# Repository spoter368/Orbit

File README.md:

# Orbit keyboard
A split ergonomic keyboard for all

#### In light of recent claims that I am 100% liable for any of my open source PCBs, I am adding this disclaimer.
#### I provide these PCBs as a reference for designing keyboard PCBs. Using them within your projects will require a will to do research of one's own and to learn the workings of them, potentially fixing issues if they exist.
# I provide these PCBs without liability and without any guarantees regarding functionality, as expressed in the licenses under which these PCBs are licensed.

## Features
- Ergonomic layout based on the [crkbd](https://github.com/foostan/crkbd)
- All on-board components; no separate controller board
- USB Type-C and in-switch backlight
- Alps SKCL/M and MX compatibility
- Built-in overcurrent, reverse voltage, and ESD protection.
- Pre-panelized in a single PCB file for easy production
- Keyboard-Layout-Editor data is available [here](http://www.keyboard-layout-editor.com/#/gists/53ebf59524de12515cb7e2e6de94f0d6).

## Designed for all
- This keyboard remains close to typical QWERTY layout in key positioning.
- Most keys remain in their typical locations, which allows easy migration from standard layout keyboards.
- Whether new to ergonomic layouts or already an avid adopter, Orbit will suit your needs.

## Electrical side
- The incoming power is handled as shown:

- VCC/Raw is the raw power fed through the USB connector. The ESD protection IC is bound to here.
- VBUS is "stable raw power" after being passed through a polyfuse. Used for upstream detection, for a downstream Schottky diode prevents flow from 5V into VBUS. In other words, VBUS is only at 5V when fed from upstream USB.
- 5V is the "stable power" after passing through a Schottky diode. Used for powering MCU, LEDs, and other split half. Power from the other half feeds here, for it has already been filtered on the other side.
- Measures are taken to isolate the LED, MCU, and split connection 5V as upstream as possible to prevent interference.

## Aesthetics
- Ground plane is limited to critical parts for aesthetic reasons.
- Top side of PCB is mostly covered with soldermask.

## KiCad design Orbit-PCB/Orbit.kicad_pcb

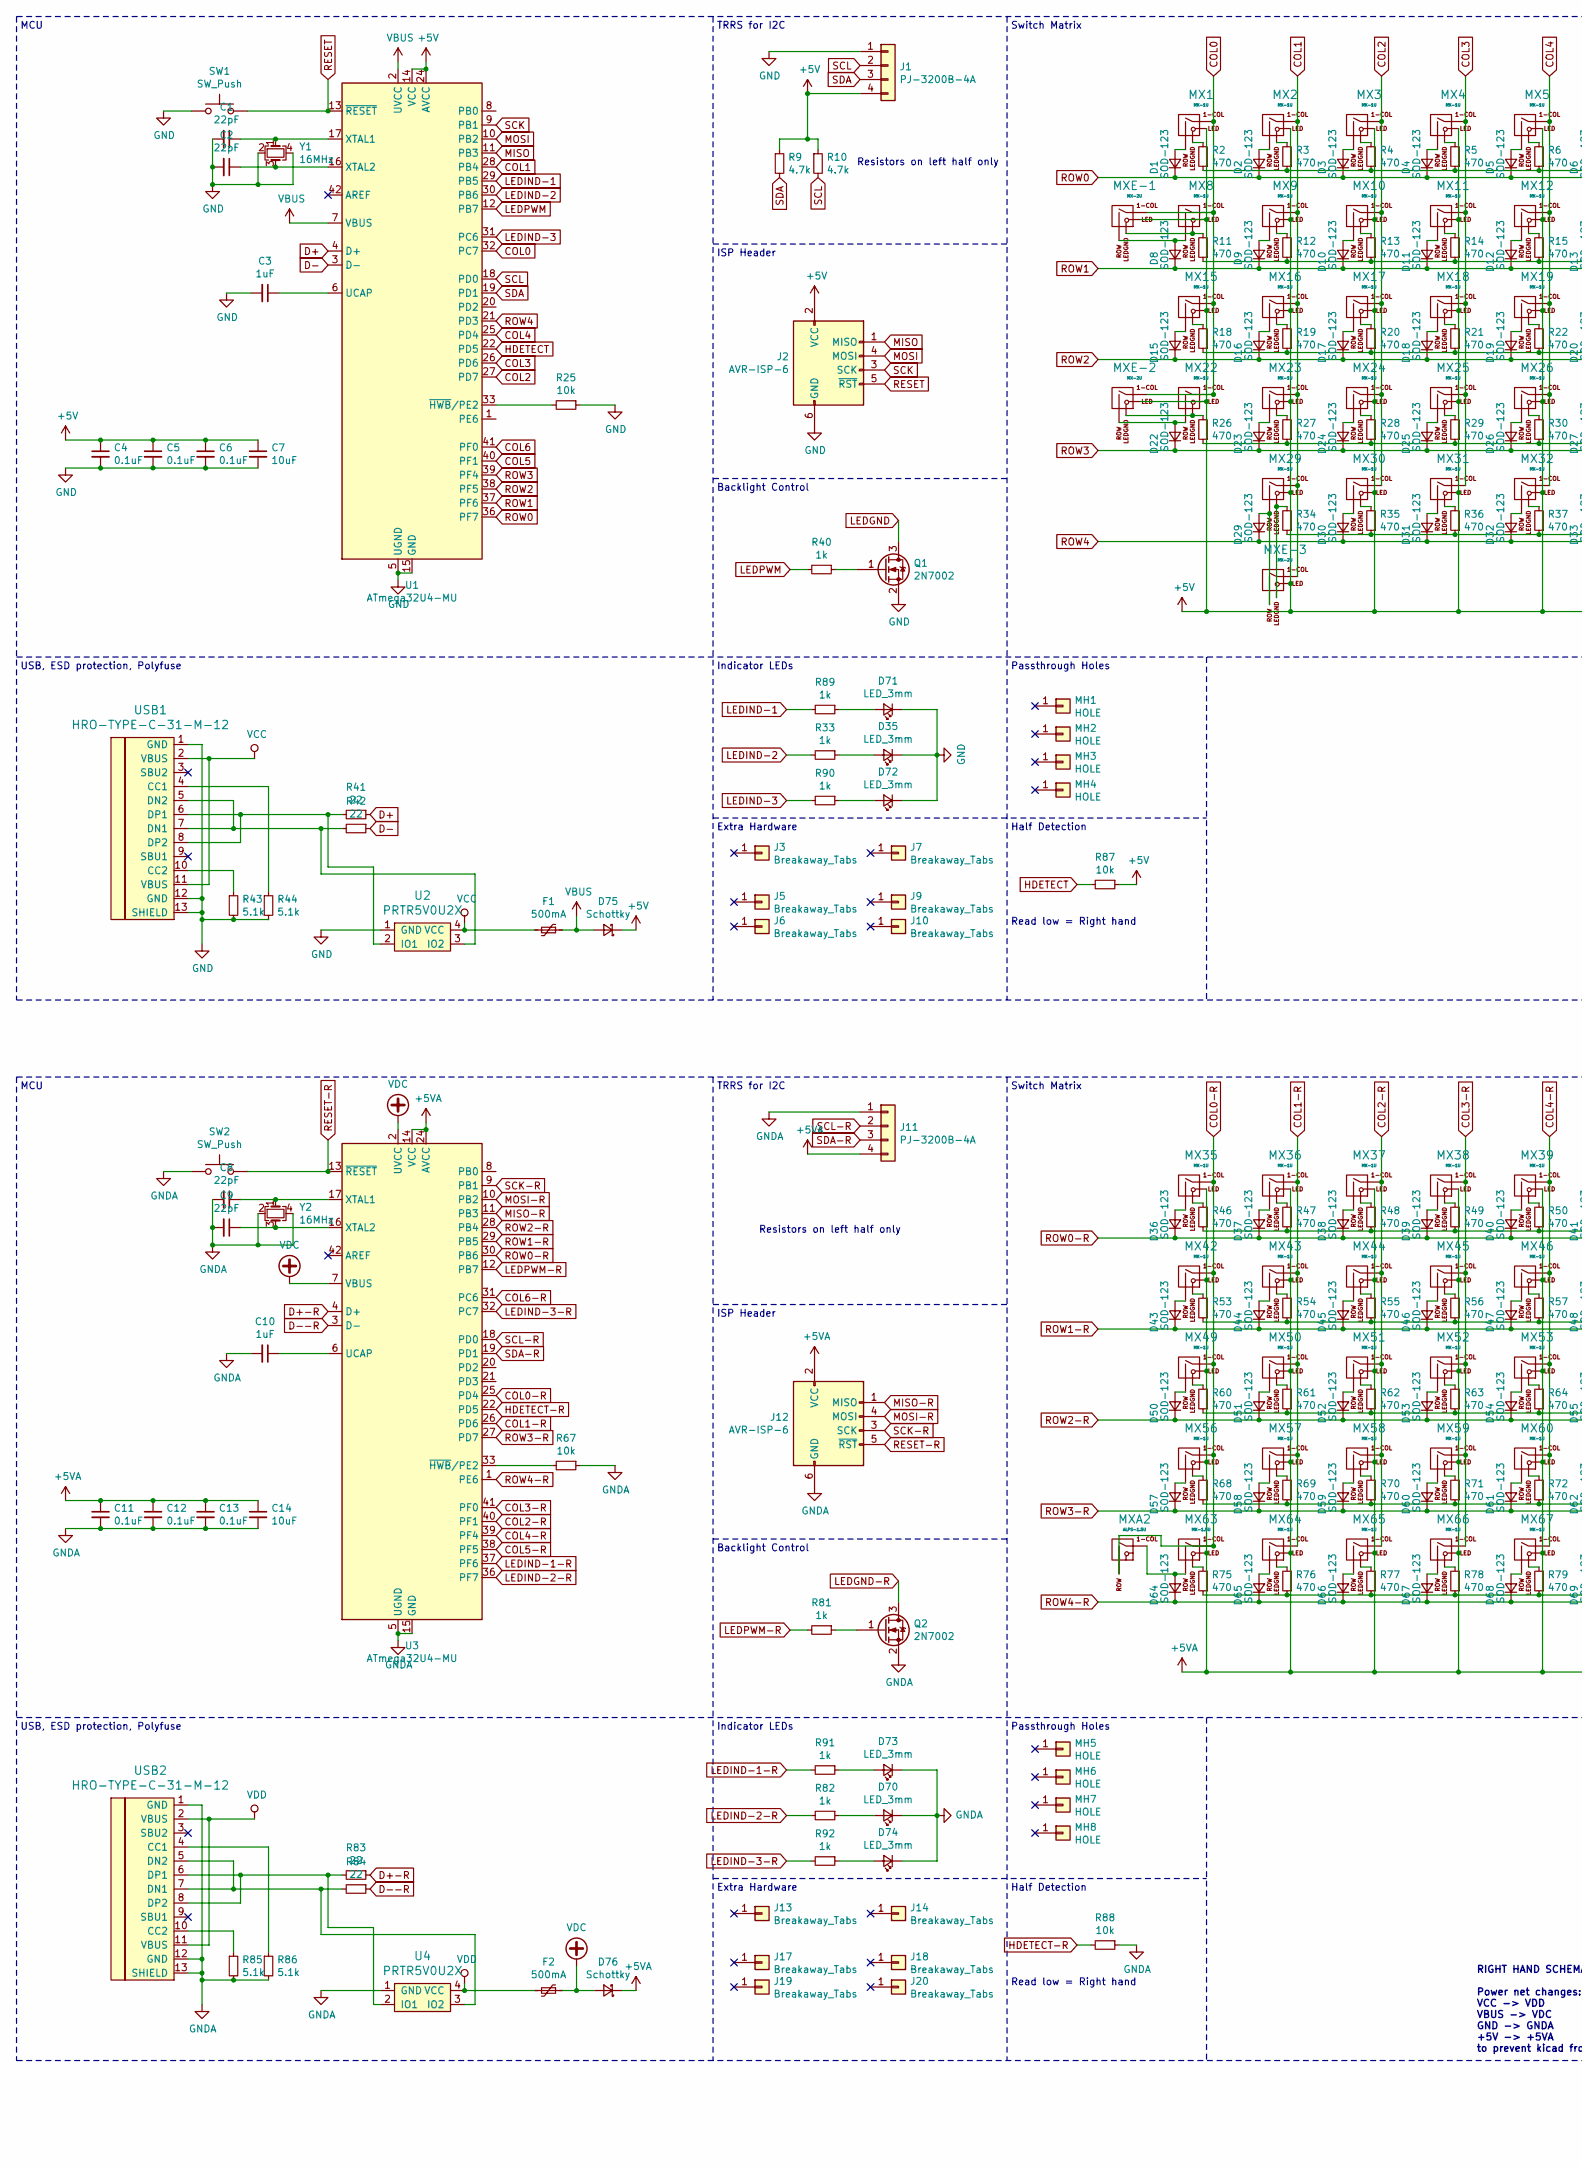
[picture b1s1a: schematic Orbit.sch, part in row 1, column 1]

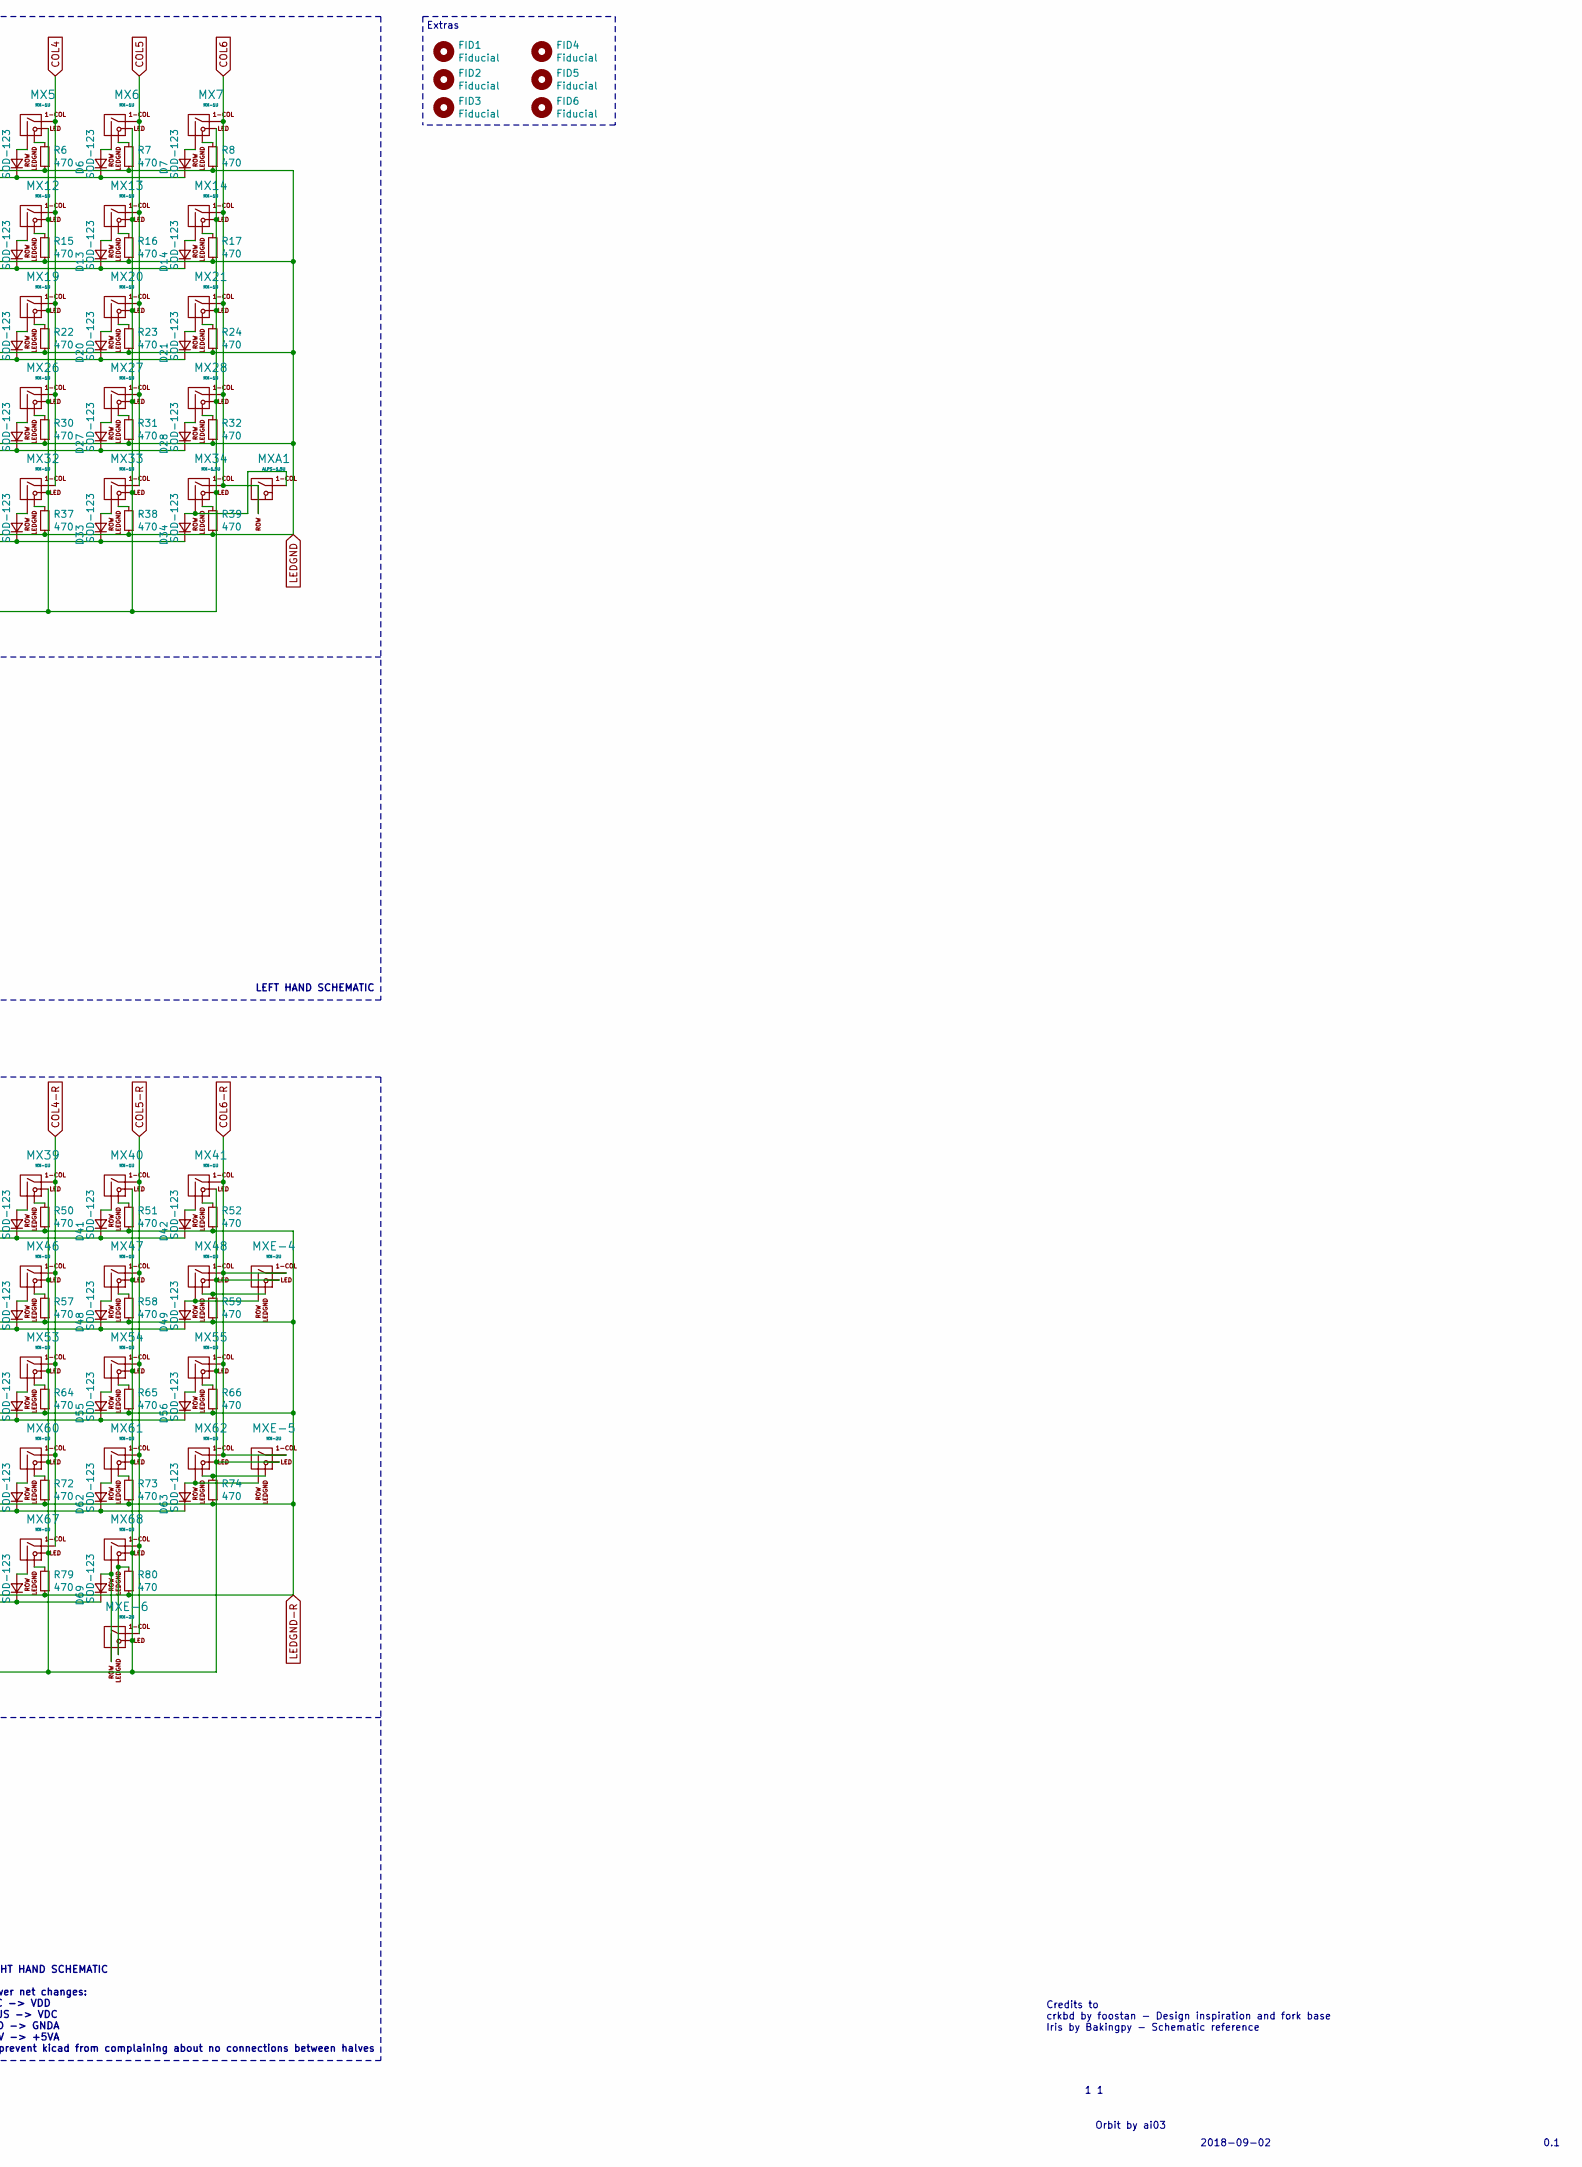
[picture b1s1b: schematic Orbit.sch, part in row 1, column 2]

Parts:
C1, C2, C8, C9: 22pF; C_0603_1608Metric
C3, C10: 1uF; C_0603_1608Metric
C4, C5, C6, C11, C12, C13: 0.1uF; C_0603_1608Metric
C7, C14: 10uF; C_0603_1608Metric
D1, D2, D3, D4, D5, D6, D7, D8, D9, D10, D11, D12, D13, D14, D15, D16, D17, D18, D19, D20, D21, D22, D23, D24, D25, D26, D27, D28, D29, D30, D31, D32, D33, D34, D36, D37, D38, D39, D40, D41, D42, D43, D44, D45, D46, D47, D48, D49, D50, D51, D52, D53, D54, D55, D56, D57, D58, D59, D60, D61, D62, D63, D64, D65, D66, D67, D68, D69: SOD-123; D_SOD-123
D35, D70, D71, D72, D73, D74: LED_3mm; LED_D3.0mm
D75, D76: Schottky; D_SOD-123
F1, F2: 500mA; Fuse_SMD1206_Reflow
FID1, FID2, FID3, FID4, FID5, FID6: Fiducial; Fiducial_1mm_Dia_2.54mm_Outer_CopperTop
J1, J11: PJ-3200B-4A
J2, J12: AVR-ISP-6; Reset_Pretty
J3, J5, J6, J7, J9, J10, J13, J14, J17, J18, J19, J20: Breakaway_Tabs; breakaway-mousebites
MH1, MH2, MH3, MH4, MH5, MH6, MH7, MH8: HOLE; MountingHole_3.2mm_M3_ISO7380
MX1, MX2, MX3, MX4, MX5, MX6, MX7, MX8, MX9, MX10, MX11, MX12, MX13, MX14, MX15, MX16, MX17, MX18, MX19, MX20, MX21, MX22, MX23, MX24, MX25, MX26, MX27, MX28, MX29, MX30, MX31, MX32, MX33, MX35, MX36, MX37, MX38, MX39, MX40, MX41, MX42, MX43, MX44, MX45, MX46, MX47, MX48, MX49, MX50, MX51, MX52, MX53, MX54, MX55, MX56, MX57, MX58, MX59, MX60, MX61, MX62, MX64, MX65, MX66, MX67, MX68: MX-1U
MX34, MX63: MX-1.5U; MXOnly-1.5U-Vertical
MXA1, MXA2: ALPS-1.5U
MXE-1, MXE-2: MX-2U
MXE-3, MXE-4, MXE-5, MXE-6: MX-2U; MX-2U-ReversedStabilizers
Q1, Q2: 2N7002; SOT-23
R2, R3, R4, R5, R6, R7, R8, R11, R12, R13, R14, R15, R16, R17, R18, R19, R20, R21, R22, R23, R24, R26, R27, R28, R29, R30, R31, R32, R34, R35, R36, R37, R38, R39, R46, R47, R48, R49, R50, R51, R52, R53, R54, R55, R56, R57, R58, R59, R60, R61, R62, R63, R64, R65, R66, R68, R69, R70, R71, R72, R73, R74, R75, R76, R77, R78, R79, R80: 470; R_0805_2012Metric
R9, R10: 4.7k; R_0805_2012Metric
R25, R67, R87, R88: 10k; R_0805_2012Metric
R33, R40, R81, R82, R89, R90, R91, R92: 1k; R_0805_2012Metric
R41, R42, R83, R84: 22; R_0805_2012Metric
R43, R44, R85, R86: 5.1k; R_0805_2012Metric
SW1, SW2: SW_Push; SKQGADE010
U1, U3: ATmega32U4-MU; QFN-44-1EP_7x7mm_Pitch0.5mm
U2, U4: PRTR5V0U2X; SOT143B
USB1, USB2: HRO-TYPE-C-31-M-12; HRO-TYPE-C-31-M-12-Assembly
Y1, Y2: 16MHz; Crystal_SMD_3225-4pin_3.2x2.5mm

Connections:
+5V: C4.1, C5.1, C6.1, C7.1, D75.1 (K), J1.4, J2.2 (VCC), MX1.3 (LED), MX2.3 (LED), MX3.3 (LED), MX4.3 (LED), MX5.3 (LED), MX6.3 (LED), MX7.3 (LED), MX8.3 (LED), MX9.3 (LED), MX10.3 (LED), MX11.3 (LED), MX12.3 (LED), MX13.3 (LED), MX14.3 (LED), MX15.3 (LED), MX16.3 (LED), MX17.3 (LED), MX18.3 (LED), MX19.3 (LED), MX20.3 (LED), MX21.3 (LED), MX22.3 (LED), MX23.3 (LED), MX24.3 (LED), MX25.3 (LED), MX26.3 (LED), MX27.3 (LED), MX28.3 (LED), MX29.3 (LED), MX30.3 (LED), MX31.3 (LED), MX32.3 (LED), MX33.3 (LED), MX34.3 (LED), MXE-1.3 (LED), MXE-2.3 (LED), MXE-3.3 (LED), R9.1, R10.1, R87.1, U1.14 (VCC), U1.24 (AVCC), U1.34 (VCC), U1.44 (AVCC)
+5VA: C11.1, C12.1, C13.1, C14.1, D76.1 (K), J11.4, J12.2 (VCC), MX35.3 (LED), MX36.3 (LED), MX37.3 (LED), MX38.3 (LED), MX39.3 (LED), MX40.3 (LED), MX41.3 (LED), MX42.3 (LED), MX43.3 (LED), MX44.3 (LED), MX45.3 (LED), MX46.3 (LED), MX47.3 (LED), MX48.3 (LED), MX49.3 (LED), MX50.3 (LED), MX51.3 (LED), MX52.3 (LED), MX53.3 (LED), MX54.3 (LED), MX55.3 (LED), MX56.3 (LED), MX57.3 (LED), MX58.3 (LED), MX59.3 (LED), MX60.3 (LED), MX61.3 (LED), MX62.3 (LED), MX63.3 (LED), MX64.3 (LED), MX65.3 (LED), MX66.3 (LED), MX67.3 (LED), MX68.3 (LED), MXE-4.3 (LED), MXE-5.3 (LED), MXE-6.3 (LED), U3.14 (VCC), U3.24 (AVCC), U3.34 (VCC), U3.44 (AVCC)
COL0: MX1.1 (COL), MX8.1 (COL), MX15.1 (COL), MX22.1 (COL), MXE-1.1 (COL), MXE-2.1 (COL), U1.32 (PC7)
COL0-R: MX35.1 (COL), MX42.1 (COL), MX49.1 (COL), MX56.1 (COL), MX63.1 (COL), MXA2.2 (ROW), U3.25 (PD4)
COL1: MX2.1 (COL), MX9.1 (COL), MX16.1 (COL), MX23.1 (COL), MX29.1 (COL), MXE-3.1 (COL), U1.28 (PB4)
COL1-R: MX36.1 (COL), MX43.1 (COL), MX50.1 (COL), MX57.1 (COL), MX64.1 (COL), U3.26 (PD6)
COL2: MX3.1 (COL), MX10.1 (COL), MX17.1 (COL), MX24.1 (COL), MX30.1 (COL), U1.27 (PD7)
COL2-R: MX37.1 (COL), MX44.1 (COL), MX51.1 (COL), MX58.1 (COL), MX65.1 (COL), U3.40 (PF1)
COL3: MX4.1 (COL), MX11.1 (COL), MX18.1 (COL), MX25.1 (COL), MX31.1 (COL), U1.26 (PD6)
COL3-R: MX38.1 (COL), MX45.1 (COL), MX52.1 (COL), MX59.1 (COL), MX66.1 (COL), U3.41 (PF0)
COL4: MX5.1 (COL), MX12.1 (COL), MX19.1 (COL), MX26.1 (COL), MX32.1 (COL), U1.25 (PD4)
COL4-R: MX39.1 (COL), MX46.1 (COL), MX53.1 (COL), MX60.1 (COL), MX67.1 (COL), U3.39 (PF4)
COL5: MX6.1 (COL), MX13.1 (COL), MX20.1 (COL), MX27.1 (COL), MX33.1 (COL), U1.40 (PF1)
COL5-R: MX40.1 (COL), MX47.1 (COL), MX54.1 (COL), MX61.1 (COL), MX68.1 (COL), MXE-6.1 (COL), U3.38 (PF5)
COL6: MX7.1 (COL), MX14.1 (COL), MX21.1 (COL), MX28.1 (COL), MX34.1 (COL), MXA1.2 (ROW), U1.41 (PF0)
COL6-R: MX41.1 (COL), MX48.1 (COL), MX55.1 (COL), MX62.1 (COL), MXE-4.1 (COL), MXE-5.1 (COL), U3.31 (PC6)
D+: R41.1, U1.4 (D+)
D+-R: R83.1, U3.4 (D+)
D-: R42.1, U1.3 (D-)
D--R: R84.1, U3.3 (D-)
GND: C1.2, C2.2, C3.2, C4.2, C5.2, C6.2, C7.2, D35.1 (K), D71.1 (K), D72.1 (K), J1.1, J2.6 (GND), Q1.2 (S), R25.1, R43.2, R44.2, SW1.1, U1.5 (UGND), U1.15 (GND), U1.23 (GND), U1.35 (GND), U1.43 (GND), U1.45 (GND), U2.1 (GND), USB1.1 (GND), USB1.12 (GND), USB1.13 (SHIELD), Y1.2, Y1.4
GNDA: C8.2, C9.2, C10.2, C11.2, C12.2, C13.2, C14.2, D70.1 (K), D73.1 (K), D74.1 (K), J11.1, J12.6 (GND), Q2.2 (S), R67.1, R85.2, R86.2, R88.1, SW2.1, U3.5 (UGND), U3.15 (GND), U3.23 (GND), U3.35 (GND), U3.43 (GND), U3.45 (GND), U4.1 (GND), USB2.1 (GND), USB2.12 (GND), USB2.13 (SHIELD), Y2.2, Y2.4
HDETECT: R87.2, U1.22 (PD5)
HDETECT-R: R88.2, U3.22 (PD5)
LEDGND: Q1.3 (D), R2.1, R3.1, R4.1, R5.1, R6.1, R7.1, R8.1, R11.1, R12.1, R13.1, R14.1, R15.1, R16.1, R17.1, R18.1, R19.1, R20.1, R21.1, R22.1, R23.1, R24.1, R26.1, R27.1, R28.1, R29.1, R30.1, R31.1, R32.1, R34.1, R35.1, R36.1, R37.1, R38.1, R39.1
LEDGND-R: Q2.3 (D), R46.1, R47.1, R48.1, R49.1, R50.1, R51.1, R52.1, R53.1, R54.1, R55.1, R56.1, R57.1, R58.1, R59.1, R60.1, R61.1, R62.1, R63.1, R64.1, R65.1, R66.1, R68.1, R69.1, R70.1, R71.1, R72.1, R73.1, R74.1, R75.1, R76.1, R77.1, R78.1, R79.1, R80.1
LEDIND-1: R89.2, U1.29 (PB5)
LEDIND-1-R: R91.2, U3.37 (PF6)
LEDIND-2: R33.2, U1.30 (PB6)
LEDIND-2-R: R82.2, U3.36 (PF7)
LEDIND-3: R90.2, U1.31 (PC6)
LEDIND-3-R: R92.2, U3.32 (PC7)
LEDPWM: R40.2, U1.12 (PB7)
LEDPWM-R: R81.2, U3.12 (PB7)
MISO: J2.1 (MISO), U1.11 (PB3)
MISO-R: J12.1 (MISO), U3.11 (PB3)
MOSI: J2.4 (MOSI), U1.10 (PB2)
MOSI-R: J12.4 (MOSI), U3.10 (PB2)
unnamed: C1.1, U1.17 (XTAL1), Y1.1
unnamed: C2.1, U1.16 (XTAL2), Y1.3
unnamed: C3.1, U1.6 (UCAP)
unnamed: C8.1, U3.17 (XTAL1), Y2.1
unnamed: C9.1, U3.16 (XTAL2), Y2.3
unnamed: C10.1, U3.6 (UCAP)
unnamed: D1.2 (A), MX1.2 (ROW)
unnamed: D2.2 (A), MX2.2 (ROW)
unnamed: D3.2 (A), MX3.2 (ROW)
unnamed: D4.2 (A), MX4.2 (ROW)
unnamed: D5.2 (A), MX5.2 (ROW)
unnamed: D6.2 (A), MX6.2 (ROW)
unnamed: D7.2 (A), MX7.2 (ROW)
unnamed: D8.2 (A), MX8.2 (ROW), MXE-1.2 (ROW)
unnamed: D9.2 (A), MX9.2 (ROW)
unnamed: D10.2 (A), MX10.2 (ROW)
unnamed: D11.2 (A), MX11.2 (ROW)
unnamed: D12.2 (A), MX12.2 (ROW)
unnamed: D13.2 (A), MX13.2 (ROW)
unnamed: D14.2 (A), MX14.2 (ROW)
unnamed: D15.2 (A), MX15.2 (ROW)
unnamed: D16.2 (A), MX16.2 (ROW)
unnamed: D17.2 (A), MX17.2 (ROW)
unnamed: D18.2 (A), MX18.2 (ROW)
unnamed: D19.2 (A), MX19.2 (ROW)
unnamed: D20.2 (A), MX20.2 (ROW)
unnamed: D21.2 (A), MX21.2 (ROW)
unnamed: D22.2 (A), MX22.2 (ROW), MXE-2.2 (ROW)
unnamed: D23.2 (A), MX23.2 (ROW)
unnamed: D24.2 (A), MX24.2 (ROW)
unnamed: D25.2 (A), MX25.2 (ROW)
unnamed: D26.2 (A), MX26.2 (ROW)
unnamed: D27.2 (A), MX27.2 (ROW)
unnamed: D28.2 (A), MX28.2 (ROW)
unnamed: D29.2 (A), MX29.2 (ROW), MXE-3.2 (ROW)
unnamed: D30.2 (A), MX30.2 (ROW)
unnamed: D31.2 (A), MX31.2 (ROW)
unnamed: D32.2 (A), MX32.2 (ROW)
unnamed: D33.2 (A), MX33.2 (ROW)
unnamed: D34.2 (A), MX34.2 (ROW), MXA1.1 (COL)
unnamed: D35.2 (A), R33.1
unnamed: D36.2 (A), MX35.2 (ROW)
unnamed: D37.2 (A), MX36.2 (ROW)
unnamed: D38.2 (A), MX37.2 (ROW)
unnamed: D39.2 (A), MX38.2 (ROW)
unnamed: D40.2 (A), MX39.2 (ROW)
unnamed: D41.2 (A), MX40.2 (ROW)
unnamed: D42.2 (A), MX41.2 (ROW)
unnamed: D43.2 (A), MX42.2 (ROW)
unnamed: D44.2 (A), MX43.2 (ROW)
unnamed: D45.2 (A), MX44.2 (ROW)
unnamed: D46.2 (A), MX45.2 (ROW)
unnamed: D47.2 (A), MX46.2 (ROW)
unnamed: D48.2 (A), MX47.2 (ROW)
unnamed: D49.2 (A), MX48.2 (ROW), MXE-4.2 (ROW)
unnamed: D50.2 (A), MX49.2 (ROW)
unnamed: D51.2 (A), MX50.2 (ROW)
unnamed: D52.2 (A), MX51.2 (ROW)
unnamed: D53.2 (A), MX52.2 (ROW)
unnamed: D54.2 (A), MX53.2 (ROW)
unnamed: D55.2 (A), MX54.2 (ROW)
unnamed: D56.2 (A), MX55.2 (ROW)
unnamed: D57.2 (A), MX56.2 (ROW)
unnamed: D58.2 (A), MX57.2 (ROW)
unnamed: D59.2 (A), MX58.2 (ROW)
unnamed: D60.2 (A), MX59.2 (ROW)
unnamed: D61.2 (A), MX60.2 (ROW)
unnamed: D62.2 (A), MX61.2 (ROW)
unnamed: D63.2 (A), MX62.2 (ROW), MXE-5.2 (ROW)
unnamed: D64.2 (A), MX63.2 (ROW), MXA2.1 (COL)
unnamed: D65.2 (A), MX64.2 (ROW)
unnamed: D66.2 (A), MX65.2 (ROW)
unnamed: D67.2 (A), MX66.2 (ROW)
unnamed: D68.2 (A), MX67.2 (ROW)
unnamed: D69.2 (A), MX68.2 (ROW), MXE-6.2 (ROW)
unnamed: D70.2 (A), R82.1
unnamed: D71.2 (A), R89.1
unnamed: D72.2 (A), R90.1
unnamed: D73.2 (A), R91.1
unnamed: D74.2 (A), R92.1
unnamed: MX1.4 (LEDGND), R2.2
unnamed: MX2.4 (LEDGND), R3.2
unnamed: MX3.4 (LEDGND), R4.2
unnamed: MX4.4 (LEDGND), R5.2
unnamed: MX5.4 (LEDGND), R6.2
unnamed: MX6.4 (LEDGND), R7.2
unnamed: MX7.4 (LEDGND), R8.2
unnamed: MX8.4 (LEDGND), MXE-1.4 (LEDGND), R11.2
unnamed: MX9.4 (LEDGND), R12.2
unnamed: MX10.4 (LEDGND), R13.2
unnamed: MX11.4 (LEDGND), R14.2
unnamed: MX12.4 (LEDGND), R15.2
unnamed: MX13.4 (LEDGND), R16.2
unnamed: MX14.4 (LEDGND), R17.2
unnamed: MX15.4 (LEDGND), R18.2
unnamed: MX16.4 (LEDGND), R19.2
unnamed: MX17.4 (LEDGND), R20.2
unnamed: MX18.4 (LEDGND), R21.2
unnamed: MX19.4 (LEDGND), R22.2
unnamed: MX20.4 (LEDGND), R23.2
unnamed: MX21.4 (LEDGND), R24.2
unnamed: MX22.4 (LEDGND), MXE-2.4 (LEDGND), R26.2
unnamed: MX23.4 (LEDGND), R27.2
unnamed: MX24.4 (LEDGND), R28.2
unnamed: MX25.4 (LEDGND), R29.2
unnamed: MX26.4 (LEDGND), R30.2
unnamed: MX27.4 (LEDGND), R31.2
unnamed: MX28.4 (LEDGND), R32.2
unnamed: MX29.4 (LEDGND), MXE-3.4 (LEDGND), R34.2
unnamed: MX30.4 (LEDGND), R35.2
unnamed: MX31.4 (LEDGND), R36.2
unnamed: MX32.4 (LEDGND), R37.2
unnamed: MX33.4 (LEDGND), R38.2
unnamed: MX34.4 (LEDGND), R39.2
unnamed: MX35.4 (LEDGND), R46.2
unnamed: MX36.4 (LEDGND), R47.2
unnamed: MX37.4 (LEDGND), R48.2
unnamed: MX38.4 (LEDGND), R49.2
unnamed: MX39.4 (LEDGND), R50.2
unnamed: MX40.4 (LEDGND), R51.2
unnamed: MX41.4 (LEDGND), R52.2
unnamed: MX42.4 (LEDGND), R53.2
unnamed: MX43.4 (LEDGND), R54.2
unnamed: MX44.4 (LEDGND), R55.2
unnamed: MX45.4 (LEDGND), R56.2
unnamed: MX46.4 (LEDGND), R57.2
unnamed: MX47.4 (LEDGND), R58.2
unnamed: MX48.4 (LEDGND), MXE-4.4 (LEDGND), R59.2
unnamed: MX49.4 (LEDGND), R60.2
unnamed: MX50.4 (LEDGND), R61.2
unnamed: MX51.4 (LEDGND), R62.2
unnamed: MX52.4 (LEDGND), R63.2
unnamed: MX53.4 (LEDGND), R64.2
unnamed: MX54.4 (LEDGND), R65.2
unnamed: MX55.4 (LEDGND), R66.2
unnamed: MX56.4 (LEDGND), R68.2
unnamed: MX57.4 (LEDGND), R69.2
unnamed: MX58.4 (LEDGND), R70.2
unnamed: MX59.4 (LEDGND), R71.2
unnamed: MX60.4 (LEDGND), R72.2
unnamed: MX61.4 (LEDGND), R73.2
unnamed: MX62.4 (LEDGND), MXE-5.4 (LEDGND), R74.2
unnamed: MX63.4 (LEDGND), R75.2
unnamed: MX64.4 (LEDGND), R76.2
unnamed: MX65.4 (LEDGND), R77.2
unnamed: MX66.4 (LEDGND), R78.2
unnamed: MX67.4 (LEDGND), R79.2
unnamed: MX68.4 (LEDGND), MXE-6.4 (LEDGND), R80.2
unnamed: Q1.1 (G), R40.1
unnamed: Q2.1 (G), R81.1
unnamed: R25.2, U1.33 (~HWB~/PE2)
unnamed: R41.2, U2.2 (IO1), USB1.6 (DP1), USB1.8 (DP2)
unnamed: R42.2, U2.3 (IO2), USB1.5 (DN2), USB1.7 (DN1)
unnamed: R43.1, USB1.10 (CC2)
unnamed: R44.1, USB1.4 (CC1)
unnamed: R67.2, U3.33 (~HWB~/PE2)
unnamed: R83.2, U4.2 (IO1), USB2.6 (DP1), USB2.8 (DP2)
unnamed: R84.2, U4.3 (IO2), USB2.5 (DN2), USB2.7 (DN1)
unnamed: R85.1, USB2.10 (CC2)
unnamed: R86.1, USB2.4 (CC1)
RESET: J2.5 (~RST), SW1.2, U1.13 (~RESET)
RESET-R: J12.5 (~RST), SW2.2, U3.13 (~RESET)
ROW0: D1.1 (K), D2.1 (K), D3.1 (K), D4.1 (K), D5.1 (K), D6.1 (K), D7.1 (K), U1.36 (PF7)
ROW0-R: D36.1 (K), D37.1 (K), D38.1 (K), D39.1 (K), D40.1 (K), D41.1 (K), D42.1 (K), U3.30 (PB6)
ROW1: D8.1 (K), D9.1 (K), D10.1 (K), D11.1 (K), D12.1 (K), D13.1 (K), D14.1 (K), U1.37 (PF6)
ROW1-R: D43.1 (K), D44.1 (K), D45.1 (K), D46.1 (K), D47.1 (K), D48.1 (K), D49.1 (K), U3.29 (PB5)
ROW2: D15.1 (K), D16.1 (K), D17.1 (K), D18.1 (K), D19.1 (K), D20.1 (K), D21.1 (K), U1.38 (PF5)
ROW2-R: D50.1 (K), D51.1 (K), D52.1 (K), D53.1 (K), D54.1 (K), D55.1 (K), D56.1 (K), U3.28 (PB4)
ROW3: D22.1 (K), D23.1 (K), D24.1 (K), D25.1 (K), D26.1 (K), D27.1 (K), D28.1 (K), U1.39 (PF4)
ROW3-R: D57.1 (K), D58.1 (K), D59.1 (K), D60.1 (K), D61.1 (K), D62.1 (K), D63.1 (K), U3.27 (PD7)
ROW4: D29.1 (K), D30.1 (K), D31.1 (K), D32.1 (K), D33.1 (K), D34.1 (K), U1.21 (PD3)
ROW4-R: D64.1 (K), D65.1 (K), D66.1 (K), D67.1 (K), D68.1 (K), D69.1 (K), U3.1 (PE6)
SCK: J2.3 (SCK), U1.9 (PB1)
SCK-R: J12.3 (SCK), U3.9 (PB1)
SCL: J1.2, R10.2, U1.18 (PD0)
SCL-R: J11.2, U3.18 (PD0)
SDA: J1.3, R9.2, U1.19 (PD1)
SDA-R: J11.3, U3.19 (PD1)
VBUS: D75.2 (A), F1.1, U1.2 (UVCC), U1.7 (VBUS)
VCC: F1.2, U2.4 (VCC), USB1.2 (VBUS), USB1.11 (VBUS)
VDC: D76.2 (A), F2.1, U3.2 (UVCC), U3.7 (VBUS)
VDD: F2.2, U4.4 (VCC), USB2.2 (VBUS), USB2.11 (VBUS)

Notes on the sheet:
ISP Header
TRRS for I2C
MCU
USB, ESD protection, Polyfuse
Resistors on left half only
Backlight Control
Switch Matrix
Orbit by ai03
1 1
2018-09-02
0.1
Credits to crkbd by foostan - Design inspiration and fork base Iris by Bakingpy - Schematic reference
Indicator LEDs
Extra Hardware
LEFT HAND SCHEMATIC
RIGHT HAND SCHEMATIC Power net changes: VCC -> VDD VBUS -> VDC GND -> GNDA +5V -> +5VA to prevent kicad from complaining about no connections between halves
Passthrough Holes
Passthrough Holes
Half Detection
Read low = Right hand
Extras

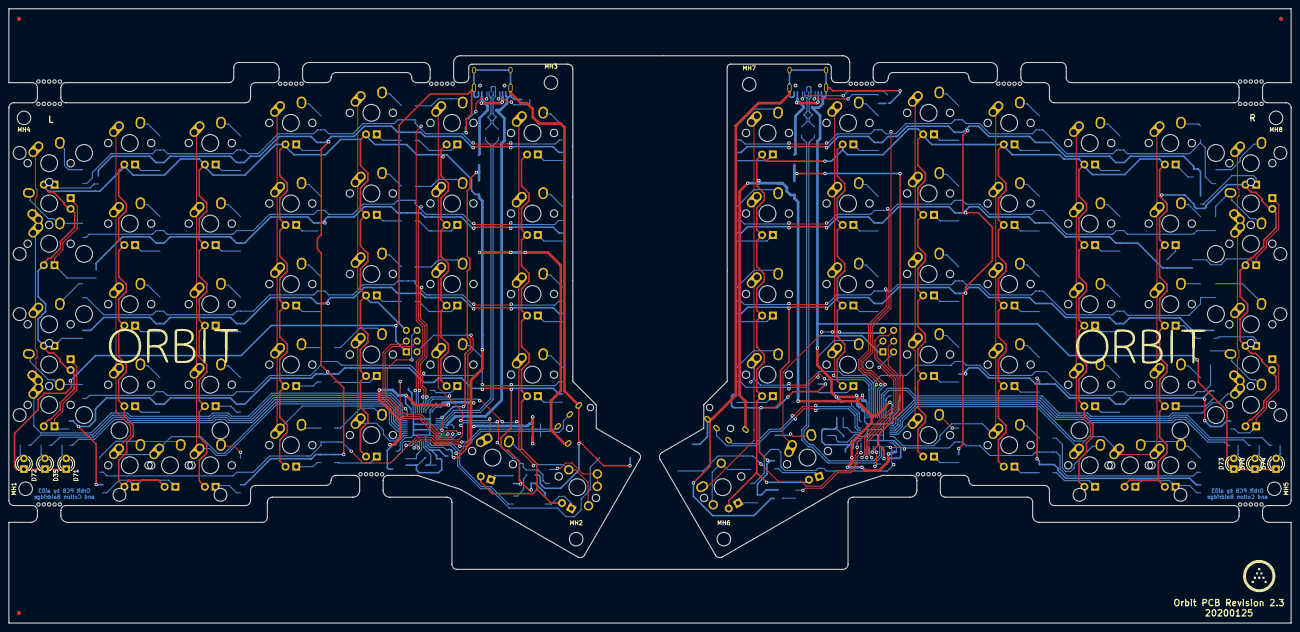
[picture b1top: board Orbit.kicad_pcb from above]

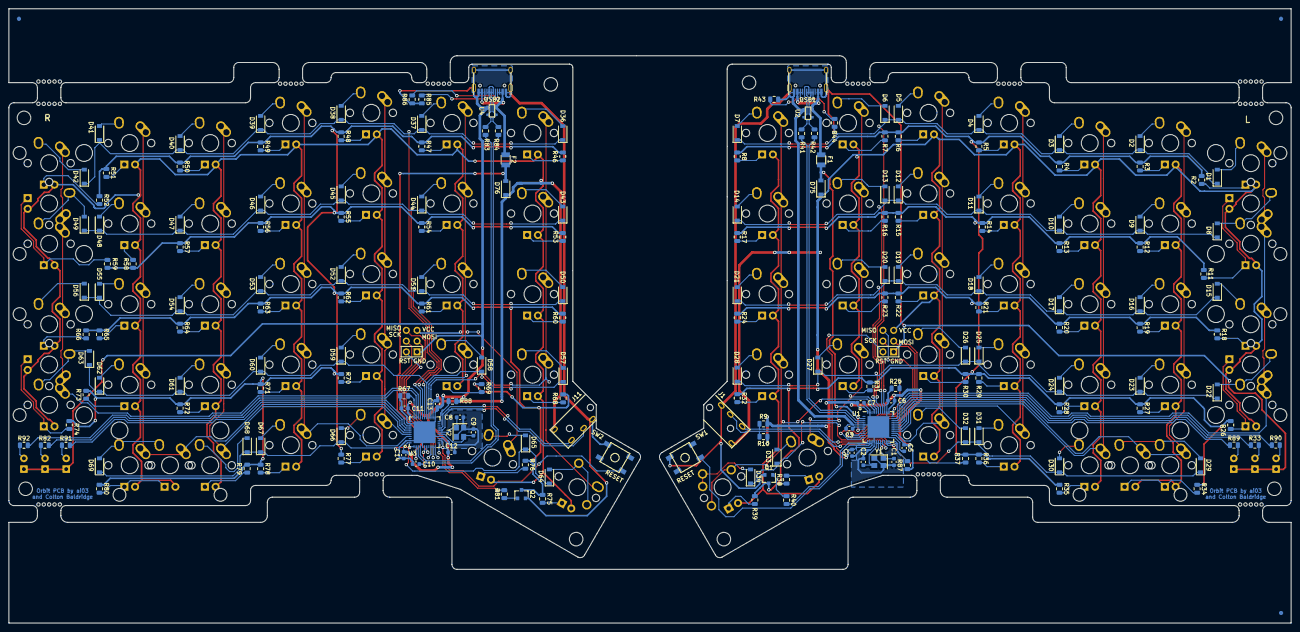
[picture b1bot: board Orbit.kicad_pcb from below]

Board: 2 copper layers, 303.2 x 145.3 mm, 300 parts (195 on the bottom side), 220 nets.

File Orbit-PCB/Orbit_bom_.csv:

Component,Description,Part,References,Value,Footprint,Quantity Per PCB,Datasheet
1,Unpolarized capacitor,C_Small,C4 C5 C6 C11 C12 C13,0.1uF,C_0603,6,~
2,Unpolarized capacitor,C_Small,C7 C14,10uF,C_0603,2,~
3,Unpolarized capacitor,C_Small,C3 C10,1uF,C_0603,2,~
4,Unpolarized capacitor,C_Small,C1 C2 C8 C9,22pF,C_0603,4,~
5,"Diode, small symbol",D_Small,D1 D2 D3 D4 D5 D6 D7 D8 D9 D10 D11 D12 D13 D14 D15 D16 D17 D18 D19 D20 D21 D22 D23 D24 D25 D26 D27 D28 D29 D30 D31 D32 D33 D34 D36 D37 D38 D39 D40 D41 D42 D43 D44 D45 D46 D47 D48 D49 D50 D51 D52 D53 D54 D55 D56 D57 D58 D59 D60 D61 D62 D63 D64 D65 D66 D67 D68 D69,SOD-123,D_SOD-123,68,~
6,"resettable fuse, polymeric positive temperature coefficient (PPTC), small symbol",Polyfuse_Small,F1 F2,500mA,Fuse_SMD1206_Reflow,2,~
7,"Generic connector, single row, 01x04, script generated (kicad-library-utils/schlib/autogen/connector/)",Conn_01x04,J1 J11,PJ-3200B-4A,PJ-3200B-4A,2,~
8,"50V Vds, 0.22A Id, N-channel MOSFET, SOT-23",2N7002,Q1 Q2,2N7002,SOT-23,2,https://www.fairchildsemi.com/datasheets/2N/2N7002.pdf
9,"Resistor, small symbol",R_Small,R1 R25 R45 R67 R87 R88,10k,R_0805,6,~
10,"Resistor, small symbol",R_Small,R33 R40 R81 R82 R89 R90 R91 R92,1k,R_0805,8,~
11,"Resistor, small symbol",R_Small,R41 R42 R83 R84,22,R_0805,4,~
12,"Resistor, small symbol",R_Small,R9 R10,4.7k,R_0805,2,~
13,"Resistor, small symbol",R_Small,R2 R3 R4 R5 R6 R7 R8 R11 R12 R13 R14 R15 R16 R17 R18 R19 R20 R21 R22 R23 R24 R26 R27 R28 R29 R30 R31 R32 R34 R35 R36 R37 R38 R39 R46 R47 R48 R49 R50 R51 R52 R53 R54 R55 R56 R57 R58 R59 R60 R61 R62 R63 R64 R65 R66 R68 R69 R70 R71 R72 R73 R74 R75 R76 R77 R78 R79 R80,470,R_0805,68,~
14,"Resistor, small symbol",R_Small,R43 R44 R85 R86,5.1k,R_0805,4,~
15,"Push button switch, generic, two pins",SW_Push,SW1 SW2,SW_Push,SKQGADE010,2,
16,"16MHz, 16kB Flash, 1.25kB SRAM, 512B EEPROM, USB 2.0, QFN-44",ATmega32U4-MU,U1 U3,ATmega32U4-MU,QFN-44-1EP_7x7mm_Pitch0.5mm,2,http://ww1.microchip.com/downloads/en/DeviceDoc/Atmel-7766-8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
17,,PRTR5V0U2X,U2 U4,PRTR5V0U2X,SOT143B,2,
18,,HRO-TYPE-C-31-M-12,USB1 USB2,HRO-TYPE-C-31-M-12,HRO-TYPE-C-31-M-12-Assembly,2,
19,"Four pin crystal, two ground/package pins (pin2 and 4) small symbol",Crystal_GND24_Small,Y1 Y2,16MHz,Crystal_SMD_2520-4pin_2.5x2.0mm,2,~





Component Groups:,19
Component Count:,190
Fitted Components:,190
Number of PCBs:,1
Total components:,190
Schematic Version:,
Schematic Date:,
BoM Date:,10/8/2018 9:39:52 PM
Schematic Source:,C:\Users\Ryota\Documents\GitHub\Orbit\Orbit-PCB\Orbit.sch
KiCad Version:,Eeschema (5.0.0)

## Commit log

2018-09-01 Never mind on the name
2018-09-01 New name
2018-09-01 Temporarily move project files
2018-09-01 Add submodules
2018-09-01 Build a schematic
2018-09-01 Assign footprints
2018-09-01 Generate netlist
2018-09-01 Update submodules
2018-09-06 Route one half
2018-09-06 Round corner and route indicator LED
2018-09-06 Both halves roughly complete, begin cleaning
2018-09-06 Reroute some traces
2018-09-06 Repair DRC errors
2018-09-06 Clean a few more traces
2018-09-06 Add left/right hand detection pullup/downs
2018-09-06 Clean a few tracks
2018-09-06 Wrong versioning
2018-09-06 Fix rail length, add dimensions
2018-09-07 Add 2U compat
2018-09-07 Reposition components to prevent stabilizer issues
2018-09-07 Prettify component labels
2018-09-07 Revision 0.2
2018-09-07 Aesthetic reroute and DRC error reduction
2018-09-07 Prettify LED power traces
2018-09-07 Fix 1.5U spacebar alps support
2018-09-07 Compact the panel slightly
2018-09-07 Simplify outline
2018-09-07 Fix trace too close to edge
2018-09-07 Upload render
2018-09-07 Edit readme
2018-09-07 List this section to prevent wall of text
2018-09-07 Add KLE layout link
2018-09-07 Add to readme
2018-09-07 Move parts for easier soldering
2018-09-08 Move TRRS connector, too deep on most chassis
2018-09-09 Move TRRS further out
2018-09-09 Route status LEDs
2018-09-09 Adjust silkscreen
2018-09-09 Clean traces, finish silkscreen
2018-09-09 Add R1.2 screenshot
2018-09-09 Beautify some traces
2018-09-09 Generate gerbers
2018-09-09 Prepare for bom generation
2018-09-09 Generate generic bom
2018-09-09 Clean BOM
2018-09-09 Generate DXF; Attempt to generate position file
2018-09-09 Attempt 2
2018-09-10 Mark some footprints as virtual or SMD for sake of position file
2018-09-10 Slight routing tweaks
2018-09-10 Further routing tweaks
2018-09-10 Further tweaking, close to complete
2018-09-10 New gerbers and position files, prepare R1.5
2018-09-10 Replace cover image
2018-09-10 Add license
2018-09-12 Update locallib readme
    Amtra's credits went to the 60% outline which is not included in this copy
2018-09-25 Nudge just a few traces
2018-09-27 One tiny ground fill change
    Remove keepout from frontside which was placed by accident
2018-10-02 Move USB connectors outwards
    Prevent conflict with switches above
2018-10-12 Production adjustments
2018-11-10 Export step
2018-11-11 Remove zones
2018-11-12 Progress
2018-11-12 Continued progress
2018-11-12 Add schottky divide to vcc/vbus
2018-11-13 Finish routing
2018-11-13 Finish reroute
2018-11-13 Final touch
2018-11-13 Please commit properly this time
2018-11-13 Recovering lost progress
2018-11-13 Cleanup
2018-11-13 Add certain footprints to locallib
2018-11-13 Further tuning
2018-11-13 Aesthetic tweaks, ready R2.0
2018-11-13 New production data
2018-11-13 Generate new BOM
2018-11-13 Update production data
2018-11-13 New cover image
2018-11-13 Add a comment
2018-11-13 Whoops
2018-11-13 Add DC reverse ratings to production spec schottky
2018-11-13 Make it export USB position
2018-11-18 Tweak routing, move reset ever so slightly
2018-11-18 Add description of power handling
2018-11-18 Fix syntax
2018-11-18 Tune routing
2018-11-18 Tune routing further
2018-11-18 Revision 2.0.1
2018-11-18 Generate 2.1 production data
2018-11-18 Correct crystal
2018-12-11 Update PCB to V2.2 - Differing pinout on each half
2018-12-11 Further tweak routing
2018-12-11 Fix some questionable design decisions
2018-12-13 Clean up decorations
2018-12-13 Generate Revision 2.2 production data
2019-01-30 Add choc variant
2019-01-30 New C conns
2019-01-30 Update submod
2019-01-31 Build Orbit-C PCB for Choc switches
2019-01-31 Update traces
2019-01-31 Adjust silkscren legends
2019-05-27 Push progress
2019-06-25 Start work on OrbitX
2019-06-25 Place switches, draw outline
2019-06-25 Generate BOM
2019-06-25 Add copper pour below USB
2019-09-02 Fixed errors in board outline
    Opened in latest version of KiCAD and fized errors that prevented 3D view from showing properly
2020-01-26 Added mounting holes at the corners
